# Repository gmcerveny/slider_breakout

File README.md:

# Slider Breakout PCB

Designed for use in prototyping creative musical interfaces.  Great
for cross faders, levels, synthesizers, sequencers, or transport
control.

This PCB design is a breakout board for a Bourns PTA3043-2015CPB103
30mm slide potentiometer.  

The breakout board design utilizes staggered jumpers so the board may
be placed vertically or horizontally on a breadboard.

The pin outs are mirrored so that if the physical direction of the
board is rotated, the resistance pins will be swapped. This allows a
user to change the direction of a slider without altering other
aspects of the circuit or software design.

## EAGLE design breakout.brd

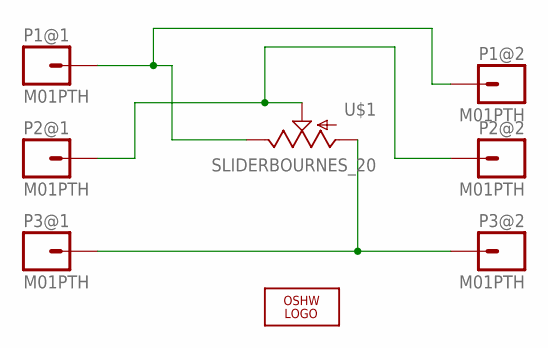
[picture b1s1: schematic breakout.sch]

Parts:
LOGO1: OSHW_LOGO_FILLX0100-NT; OSHW_FILLX100_NOTEXT
P1@1, P1@2, P2@1, P2@2, P3@1, P3@2: M01PTH; 1X01
U$1: SLIDERBOURNES_20; BOURNS_20

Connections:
unnamed: P2@1.1, P2@2.1, U$1.P$2 (S)
unnamed: P3@1.1, P3@2.1, U$1.P$3 (A)
unnamed: P1@1.1, P1@2.1, U$1.P$1 (E)

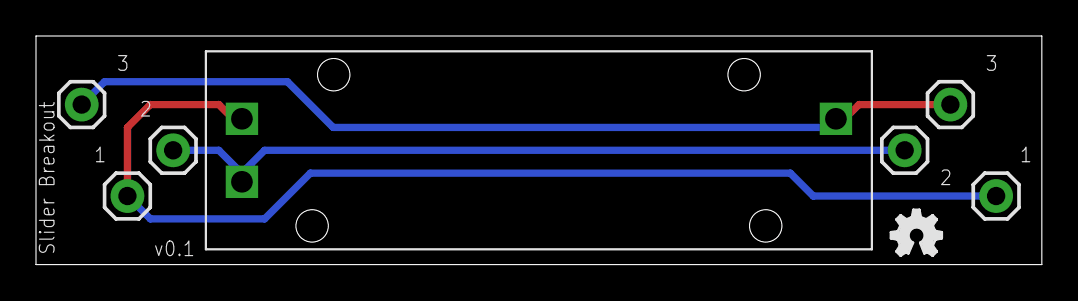
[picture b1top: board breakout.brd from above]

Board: 2 copper layers, 55.9 x 12.7 mm, 8 parts (0 on the bottom side), 3 nets.

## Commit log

2013-09-09 initializing repo
2013-09-09 adding readme
2013-09-09 adding data sheet
2013-09-09 removing eagle noise
2013-09-10 ignoring eagle noise
2013-09-10 increasing font and oshw logo size
2013-09-10 increasing trace to 16 mil because why not
2013-09-10 adding tolerance to slider tab drill holes
2013-09-10 adding rendered pcb image
2013-09-10 adding screenshot to README
2013-09-10 fixing image tag
2013-09-10 Adding board alt text

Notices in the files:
parts and their libraries:
SparkFun-Connectors: Licensing: CC v3.0 Share-Alike You are welcome to use this library for commercial purposes.
